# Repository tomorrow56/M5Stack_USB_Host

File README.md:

# M5Stack_USB_Host

Web site: [https://thousandiy.wordpress.com/2018/06/16/usb-host-for-m5stack/](https://thousandiy.wordpress.com/2018/06/16/usb-host-for-m5stack/)

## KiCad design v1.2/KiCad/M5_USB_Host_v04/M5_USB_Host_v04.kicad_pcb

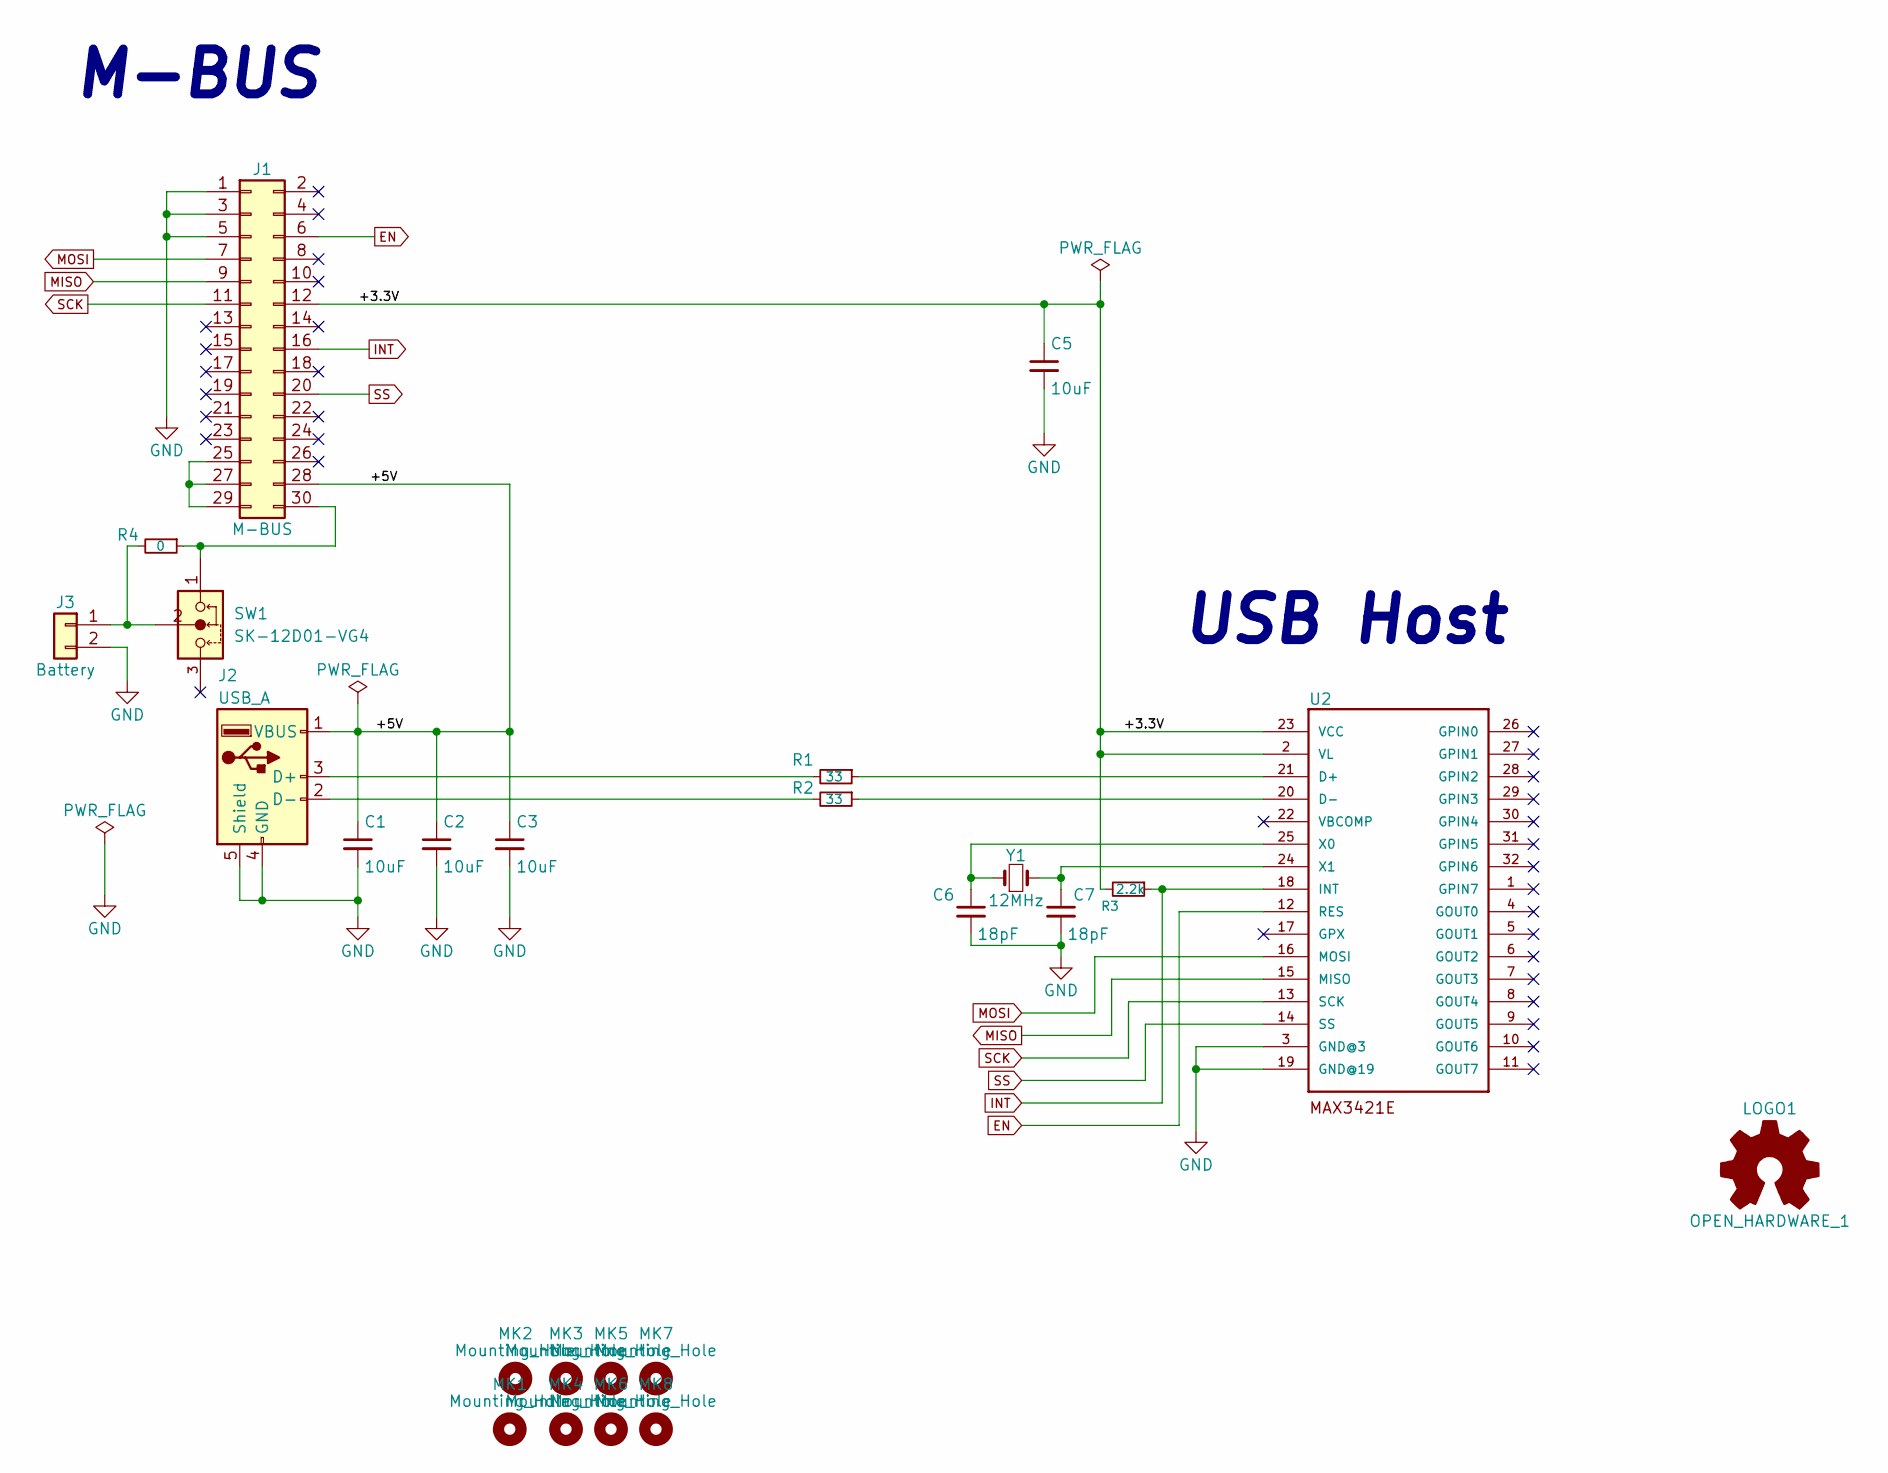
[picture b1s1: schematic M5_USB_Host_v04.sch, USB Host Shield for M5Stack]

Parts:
C1, C2, C3, C5: 10uF; C_0603
C6, C7: 18pF; C_0603
J1: M-BUS; Pin_Header_MBUS_SMD_TH
J2: USB_A
J3: Battery; Pin_Header_Angled_1x02_Pitch2.54mm
LOGO1: OPEN_HARDWARE_1; OSHW-logo_silkscreen-front_3mm
MK1, MK2, MK3, MK4: Mounting_Hole; MountingHole_3.2mm_M3
MK5, MK6, MK7, MK8: Mounting_Hole; MountingHole_2.2mm_M2
R1, R2: 33; R_0603
R3: 2.2k; R_0603
R4: 0; R_0603
SW1: SK-12D01-VG4; slide_switch_angled
U2: MAX3421E; MAX3421E_TQFP32-5MM
Y1: 12MHz; Crystal_SMD_5032-2pin_5.0x3.2mm

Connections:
/+3.3V: C5.1, J1.12, R3.2, U2.2 (VL), U2.23 (VCC)
/+5V: C1.1, C2.1, C3.1, J1.28, J2.1 (VBUS)
EN: J1.6, U2.12 (RES)
GND: C1.2, C2.2, C3.2, C5.2, C6.2, C7.2, J1.1, J1.3, J1.5, J2.4 (GND), J2.5 (Shield), J3.2, U2.3 (GND@3), U2.19 (GND@19)
INT: J1.16, R3.1, U2.18 (INT)
MISO: J1.9, U2.15 (MISO)
MOSI: J1.7, U2.16 (MOSI)
unnamed: C6.1, U2.25 (X0), Y1.1
unnamed: C7.1, U2.24 (X1), Y1.2
unnamed: J1.25, J1.27, J1.29
unnamed: J1.30, R4.1, SW1.1
unnamed: J2.2 (D-), R2.2
unnamed: J2.3 (D+), R1.2
unnamed: J3.1, R4.2, SW1.2
unnamed: R1.1, U2.21 (D+)
unnamed: R2.1, U2.20 (D-)
SCK: J1.11, U2.13 (SCK)
SS: J1.20, U2.14 (SS)

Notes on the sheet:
M-BUS
USB Host

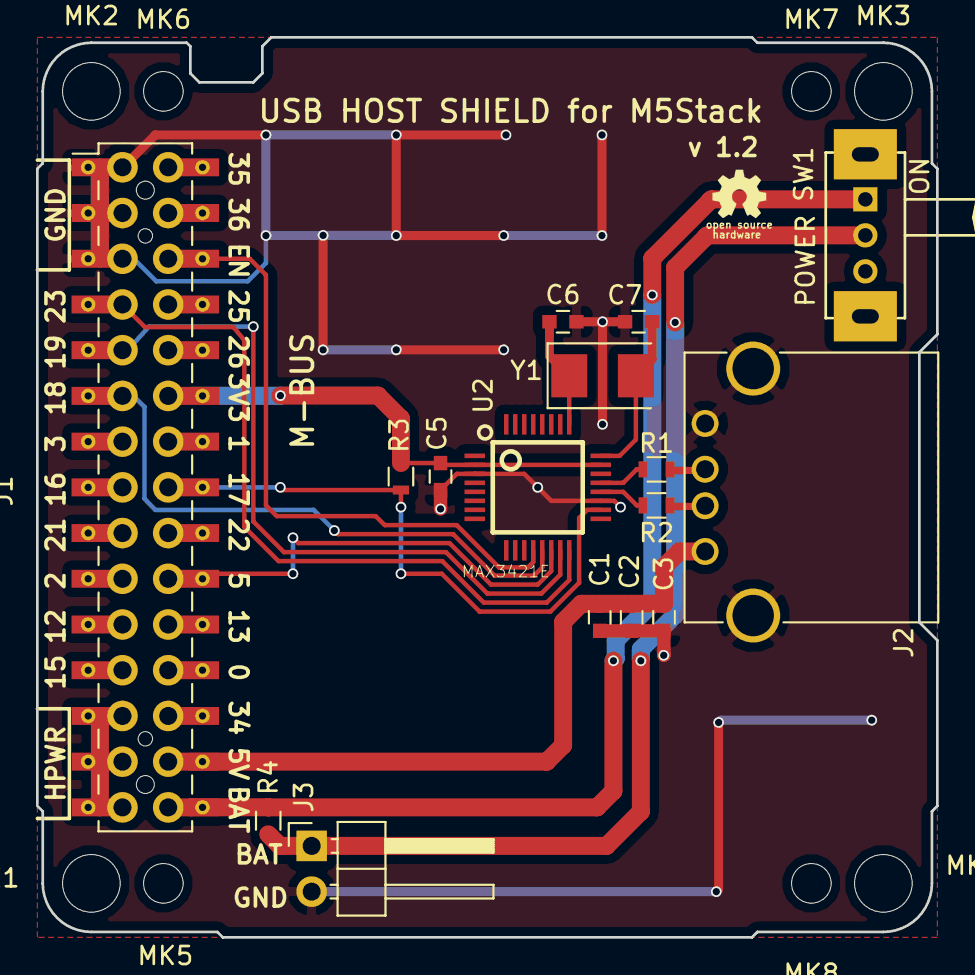
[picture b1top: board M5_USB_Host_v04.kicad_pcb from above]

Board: 2 copper layers, 50.0 x 50.0 mm, 25 parts (0 on the bottom side), 18 nets.

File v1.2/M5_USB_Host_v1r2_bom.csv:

Reference, Value, Footprint, Datasheet, フィールド4
"C2","10uF","Capacitors_SMD:C_0603",""
"C3","10uF","Capacitors_SMD:C_0603",""
"C1","10uF","Capacitors_SMD:C_0603",""
"C5","10uF","Capacitors_SMD:C_0603",""
"J2","USB_A","Connectors:USB_A",""
"R1","33","Resistors_SMD:R_0603",""
"R2","33","Resistors_SMD:R_0603",""
"Y1","12MHz","Crystals:Crystal_SMD_5032-2pin_5.0x3.2mm",""
"C7","18pF","Capacitors_SMD:C_0603",""
"C6","18pF","Capacitors_SMD:C_0603",""
"R3","2.2k","Resistors_SMD:R_0603",""
"J1","M-BUS","footprint:Pin_Header_MBUS_SMD_TH",""
"J3","Battery","Pin_Headers:Pin_Header_Angled_1x02_Pitch2.54mm",""
"U2","MAX3421E","footprint:MAX3421E_TQFP32-5MM","1.2v To +5.5v, ±15kv Esd-Protected, 0.1µa, 35mbps, 8-Channel Level Translators","Maxim Integrated"
"MK2","Mounting_Hole","Mounting_Holes:MountingHole_3.2mm_M3",""
"MK3","Mounting_Hole","Mounting_Holes:MountingHole_3.2mm_M3",""
"MK5","Mounting_Hole","Mounting_Holes:MountingHole_2.2mm_M2",""
"MK7","Mounting_Hole","Mounting_Holes:MountingHole_2.2mm_M2",""
"MK1","Mounting_Hole","Mounting_Holes:MountingHole_3.2mm_M3",""
"MK4","Mounting_Hole","Mounting_Holes:MountingHole_3.2mm_M3",""
"MK6","Mounting_Hole","Mounting_Holes:MountingHole_2.2mm_M2",""
"MK8","Mounting_Hole","Mounting_Holes:MountingHole_2.2mm_M2",""
"LOGO1","OPEN_HARDWARE_1","footprint:OSHW-logo_silkscreen-front_3mm",""
"SW1","SK-12D01-VG4","footprint:slide_switch_angled","http://akizukidenshi.com/download/ds/jianfu/SK-12D01-VG4.pdf"
"R4","0","Resistors_SMD:R_0603",""

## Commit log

2018-07-13 Nt Kanazawa 2018 version
2018-09-24 add v1.2 for Switch Science
2018-10-15 add Host shield case data
2018-10-15 add photo
2018-10-15 add readme.md
2018-11-18 add DMM.make Link of Creator's Market
2018-11-18 add DMM.make Creator's Market
